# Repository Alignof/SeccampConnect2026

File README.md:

# SeccampConnect2026
  Security Camp Connect 2026

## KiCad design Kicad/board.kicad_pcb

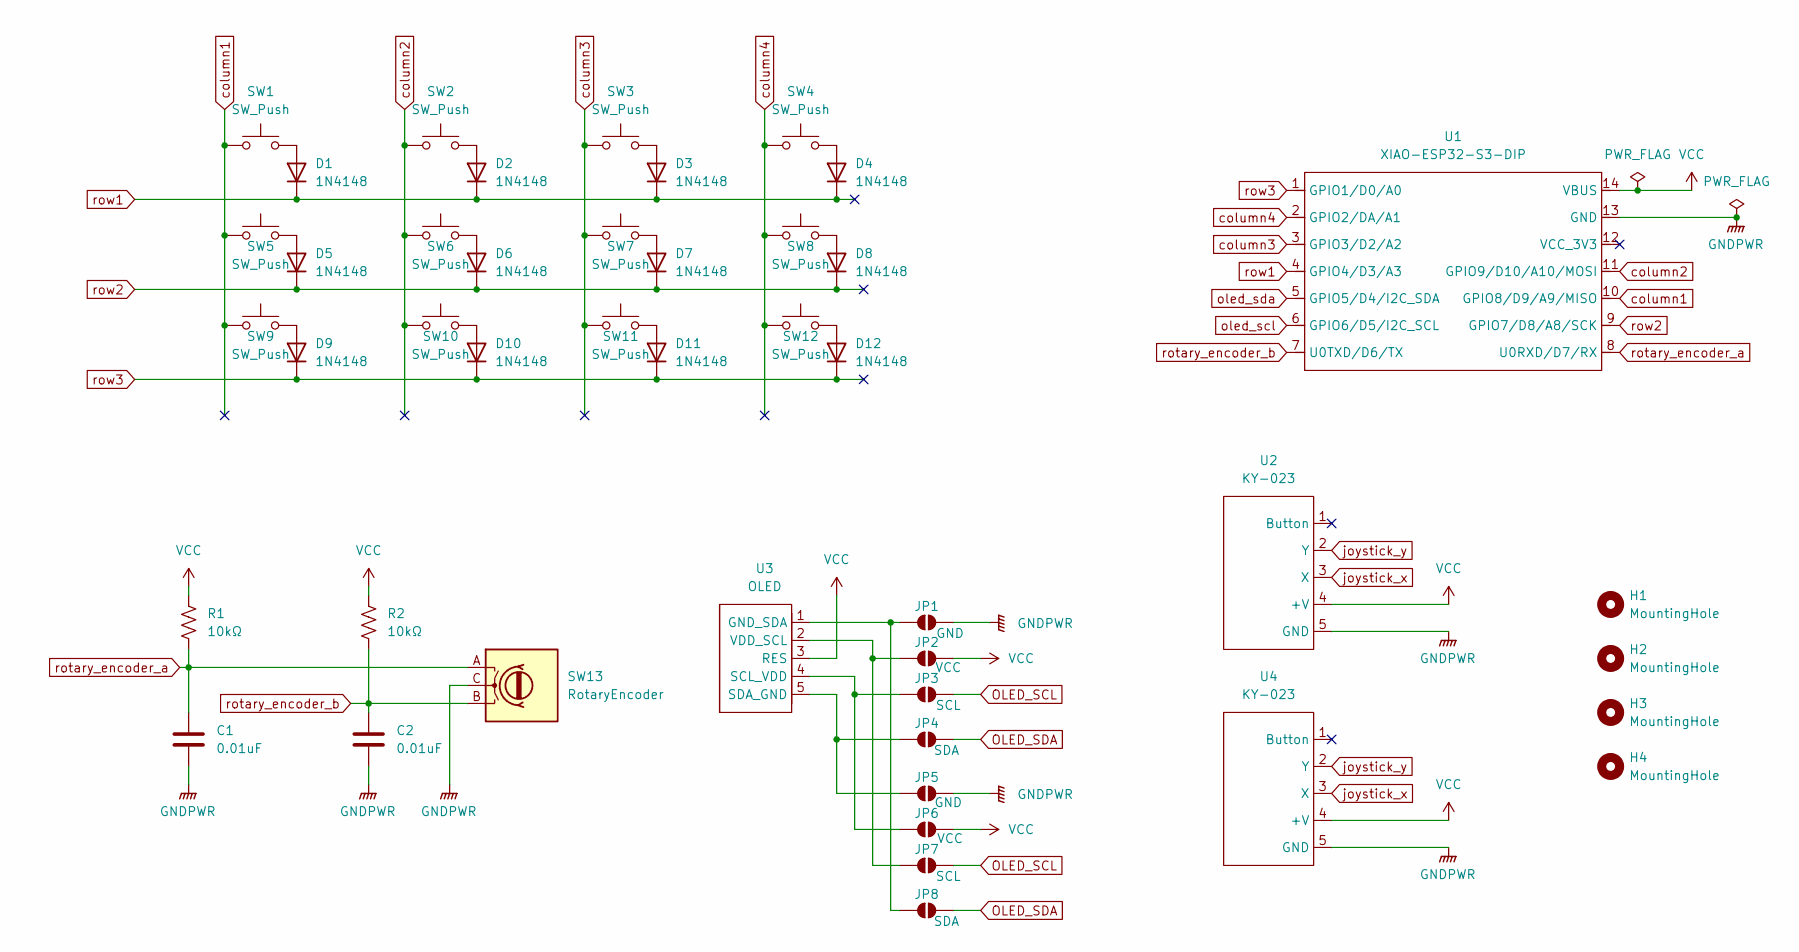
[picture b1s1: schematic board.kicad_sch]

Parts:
C1, C2: 0.01uF; C_0805_2012_HandSolder_reversible
D1, D2, D3, D4, D5, D6, D7, D8, D9, D10, D11, D12: 1N4148; Diode_THT_reversible
H1, H2, H3, H4: MountingHole; MountingHole_2.7mm
JP1, JP5: GND; SolderJumper-2_P1.3mm_Open_TrianglePad1.0x1.5mm
JP2, JP6: VCC; SolderJumper-2_P1.3mm_Open_TrianglePad1.0x1.5mm
JP3, JP7: SCL; SolderJumper-2_P1.3mm_Open_TrianglePad1.0x1.5mm
JP4, JP8: SDA; SolderJumper-2_P1.3mm_Open_TrianglePad1.0x1.5mm
R1, R2: 10kΩ; R_L6.3mm_D2.5mm_P10.16mm_Horizontal_reversible
SW1, SW2, SW3, SW4, SW5, SW6, SW7, SW8, SW9, SW10, SW11, SW12: SW_Push; Kailh_socket_PG1350_optional_reversible
SW13: RotaryEncoder; RotaryEncoder_Alps_EC12E_Vertical_H20mm
U1: XIAO-ESP32-S3-DIP; XIAO-ESP32S3-DIP
U2, U4: KY-023
U3: OLED; PinSocket_1x05_P2.54mm_Vertical

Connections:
GNDPWR: C1.2, C2.2, JP1.2 (B), JP5.2 (B), SW13.C, U1.13 (GND), U2.5 (GND), U4.5 (GND)
unnamed: D1.2 (A), SW1.2
unnamed: D2.2 (A), SW2.2
unnamed: D3.2 (A), SW3.2
unnamed: D4.2 (A), SW4.2
unnamed: D5.2 (A), SW5.2
unnamed: D6.2 (A), SW6.2
unnamed: D7.2 (A), SW7.2
unnamed: D8.2 (A), SW8.2
unnamed: D9.2 (A), SW9.2
unnamed: D10.2 (A), SW10.2
unnamed: D11.2 (A), SW11.2
unnamed: D12.2 (A), SW12.2
unnamed: JP1.1 (A), JP8.1 (A), U3.1 (GND_SDA)
unnamed: JP2.1 (A), JP7.1 (A), U3.2 (VDD_SCL)
unnamed: JP3.1 (A), JP6.1 (A), U3.4 (SCL_VDD)
unnamed: JP4.1 (A), JP5.1 (A), U3.5 (SDA_GND)
unnamed: U2.2 (Y), U4.2 (Y)
unnamed: U2.3 (X), U4.3 (X)
OLED_SCL: JP3.2 (B), JP7.2 (B)
OLED_SDA: JP4.2 (B), JP8.2 (B)
VCC: JP2.2 (B), JP6.2 (B), R1.1, R2.1, U1.14 (VBUS), U2.4 (+V), U3.3 (RES), U4.4 (+V)
column1: SW1.1, SW5.1, SW9.1, U1.10 (GPIO8/D9/A9/MISO)
column2: SW2.1, SW6.1, SW10.1, U1.11 (GPIO9/D10/A10/MOSI)
column3: SW3.1, SW7.1, SW11.1, U1.3 (GPIO3/D2/A2)
column4: SW4.1, SW8.1, SW12.1, U1.2 (GPIO2/DA/A1)
oled_scl: U1.6 (GPIO6/D5/I2C_SCL)
oled_sda: U1.5 (GPIO5/D4/I2C_SDA)
rotary_encoder_a: C1.1, R1.2, SW13.A, U1.8 (U0RXD/D7/RX)
rotary_encoder_b: C2.1, R2.2, SW13.B, U1.7 (U0TXD/D6/TX)
row1: D1.1 (K), D2.1 (K), D3.1 (K), D4.1 (K), U1.4 (GPIO4/D3/A3)
row2: D5.1 (K), D6.1 (K), D7.1 (K), D8.1 (K), U1.9 (GPIO7/D8/A8/SCK)
row3: D9.1 (K), D10.1 (K), D11.1 (K), D12.1 (K), U1.1 (GPIO1/D0/A0)

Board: 2 copper layers, 43 parts (4 on the bottom side), 29 nets, no tracks yet.

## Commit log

2025-10-08 [add] define development environment
2025-10-08 [add] init cargo project
2025-10-08 [fix] fix toolchain version
2025-10-08 [fix] add esp-bootloader-esp-idf and update some crates version
2025-10-08 [update] update keymap data
2025-12-20 [update] update rust toolchain
2025-12-20 [wip][update] update rmk version to 0.8.2
2025-12-20 [add] support for rotary encoder
2025-12-20 [add] add Fritzing data
2025-12-26 [add] add kicad data
2025-12-28 [add] add my library
2026-01-01 [add] add through hole
2026-01-01 [update] move diodes
2026-01-01 [update] move key layout
2026-01-01 [update] routed
2026-01-02 [add] add sign to silk layer
2026-01-02 [add] add jlcpcb data
2026-02-25 [add] support for joystick
2026-02-25 [add] add building docker container script
2026-03-04 [update] modify pin assign to match pcb specification
2026-03-05 [add] add lint rules
2026-03-05 [refactor] apply `cargo clippy --fix`
2026-03-05 [fix] fix a pin name of esp32s3
2026-03-06 [update] schematic in Fritzing/keyboard.fzz
2026-03-06 [add] add a github workflow for Rust
2026-03-06 [add] add vial
2026-03-06 [fix] modify docker tag to lower case
2026-03-15 [add] add my parts library
2026-03-15 [add] add an oled device and revise pin assign
2026-03-16 [update] update footprint
2026-03-17 [fix] abort waiting for download after burn flash data
2026-03-17 [add] add solder jumpers to support reversible pin holes
2026-03-17 [add] add a footprint supports both choc v1 and v2
2026-03-17 [update] update diode footprint
2026-03-17 [update] re-annotate symbols
2026-03-17 [add] add reversible footprints
2026-03-17 [update] clear the ERC
2026-03-17 [add] place parts in pcb editor
2026-03-17 [add] add XIAO-ESP32S3_reversible.kicad_mod
2026-03-17 [update] set 3D model path to Kailh key switch
2026-03-17 [update] update silk and parts placement
2026-03-17 [!][fix] fix power line connection
2026-03-18 [update] production ready
2026-03-19 [fix] modify the docker image used in github actions
2026-03-22 [add] add reviewdog to docker image for github actions
2026-03-22 [add] add bash alias for shebang
2026-03-22 [add] directly run clippy
2026-03-22 [fix] redirect stderr to stdout
2026-03-22 [fix] re-introduce clippy-reviewdog-filter
2026-03-23 [fix] add the allow macro to autogenerated codes
2026-03-23 [add] write doc comments
2026-03-23 [refactor] fix cargo clippy warnings
2026-03-24 [add] add idf.py to development shell
2026-03-24 [add] genereted `secure_bootloader` directory by `idf.py create-project secure_bootloader`
2026-03-24 [update] ignore sdkconfig.old
2026-03-24 [update] update sdkconfig via menuconfig
2026-03-24 [add] add partitions.csv
2026-03-24 [!][update] ignore symbolick link and generated signing key
2026-03-24 [!][update] enable security feature in sdkconfig
2026-03-25 [update] ignore built firmware
2026-03-25 [add] add Makefile.toml
2026-03-25 [update] configure product name
2026-03-26 [update] update default keymap
2026-03-26 [fix] fix running command
2026-03-26 [add] add `cargo-make`
2026-03-26 [fix] correct gpio assign
2026-03-26 [add] support for oled
2026-03-27 [fix] correct vial keymap to 3x4
2026-03-27 [fix] handle optional OLED display initialization and task spawning
2026-03-27 [fix] update init_oled function to return None on initialization failure
2026-03-28 [fix] export idf.py
2026-03-28 [fix] export and reconfigure idf.py
2026-03-28 [fix] update Docker image reference in devcontainer configuration
